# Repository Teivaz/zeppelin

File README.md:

# Zeppelin 

### Airship project with all electrical circuits, PCBs, blueprints, software sources and calculations

### Intended result
First version of this zeppelin should be able to keep itself up in the sky for a decent amount of time. It will be controled remotely (probably via iphone). Total length of airship 168.13cm. Volume 0.46 m3.
In the end it should look like this:    

### Progress
 - [X] Calculate the overall size, mass, and lifting force of the aerostat
 - [X] Create patterns for aerostat
 - [X] Create electrical schemas
 - [X] Design software architecture
 - [ ] Create and debug airship's software
 - [ ] Create software for controlling unit
 - [ ] Trace PCBs and make all PCBs
 - [ ] Assemble aerostat
 - [ ] Field tests

### Calculations
Here is the [link](https://docs.google.com/spreadsheets/d/1KFVUaK0Eav1PAXg2VrwWtU-BHmDxbaWGcJfdvVmI2J4/edit?usp=sharing) to spreadsheet with calculation I made for the lifting force and mass of the airship 

### Mechanics
Most parts used here were thoroughly measured and calculated. Like these cases for motors and servos (feather module)   

### Electronic schematics and PCBs
Well there's not much to say about schematics despite the fact that I'm using ST microcontroller stm32l011f4 and transmitting modules nRF24013. It is designed and traced with [EAGLE](https://www.autodesk.com/products/eagle/overview).

### Software
I am using smt32l011 and the IDE is [VS Code](https://code.visualstudio.com). The language is C with HAL library.

### Version 1.0 considerations
 * Feather MCU should use internal PWM channels directly. This will simplify code and increase working frequency.
 * Feather should use a motor driver that does not short circuit when in low phase of the PWM.
 * Consider using 8 bit controller for the Feather module.

### Further plans
 * Second version will be able to carry a camera.
 * Third version will automatically keep position, folow the route or target.

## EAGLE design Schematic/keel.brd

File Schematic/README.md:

# Change log

## Version 1.1
Status: In development
Changes:
 - [Keel] Added power regulator.
 - [Keel] Measuring Bat0 through divider.
 - [Feather] Changed pinout for PWM.

## Version 1.0.1
Status: Upgraded from v1.0.0
Changes:
 - [Keel] Replaced vertical connectors with horizontal (fixed connector pin numbers).
 - [Keel] Fixed LED polarity.
 - [Keel] Changed voltage divider resistor.
 - [Keel] Flipped the power switch.

## Version 1.0.0
Status: Manufactured

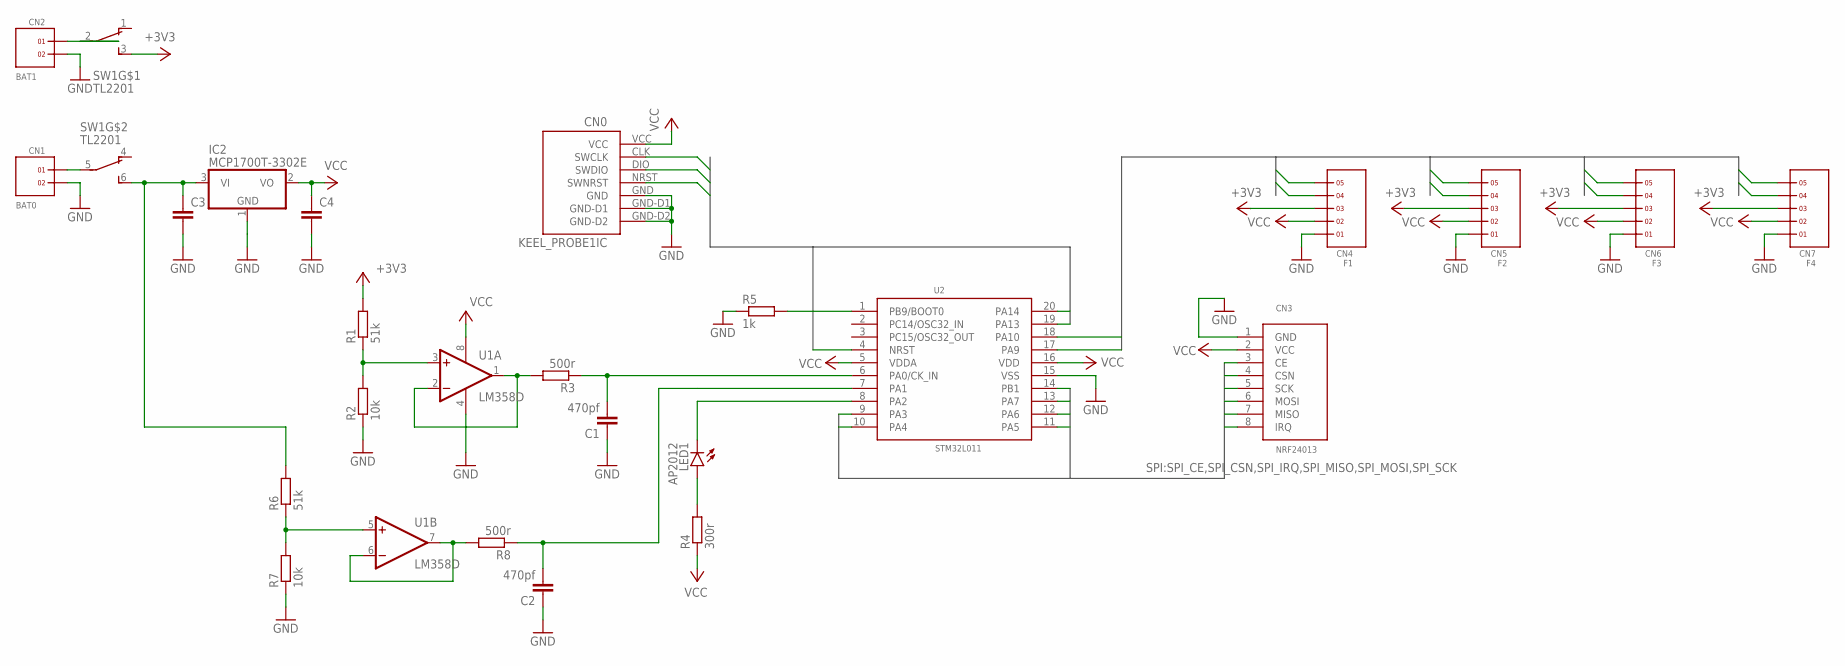
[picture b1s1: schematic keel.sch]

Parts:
C1, C2: 470pf; C0805
C3, C4: C-EUC0805; C0805
CN0: KEEL_PROBE1IC; KEEL_PROBE-IC1
CN1: BAT0; 1X2
CN2: BAT1; 1X2
CN3: NRF24013; PIN
CN4: F1; 1X5H
CN5: F2; 1X5H
CN6: F3; 1X5H
CN7: F4; 1X5H
IC2: MCP1700T-3302E; SOT23
LED1: AP2012
R1, R6: 51k; R0805
R2, R7: 10k; R0805
R3, R8: 500r; R0805
R4: 300r; R0805
R5: 1k; R0805
SW1: TL2201
U1: LM358D; SO08
U2: STM32L011; SSOP20

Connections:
+3V3: CN4.3, CN5.3, CN6.3, CN7.3, R1.2, SW1.3
GND: C1.1, C2.1, C3.2, C4.2, CN0.GND, CN0.GND-D1, CN0.GND-D2, CN1.2, CN2.2, CN3.1 (GND), CN4.1, CN5.1, CN6.1, CN7.1, IC2.1 (GND), R2.1, R5.1, R7.1, U1.4 (V-), U2.15 (VSS)
I2C_SCL: CN4.4, CN5.4, CN6.4, CN7.4, U2.17 (PA9)
I2C_SDA: CN4.5, CN5.5, CN6.5, CN7.5, U2.18 (PA10)
unnamed: R1.1, R2.2, U1.3 (+IN)
unnamed: LED1.C, U2.8 (PA2)
unnamed: LED1.A, R4.2
unnamed: C1.2, R3.1, U2.6 (PA0/CK_IN)
unnamed: R5.2, U2.1 (PB9/BOOT0)
unnamed: R3.2, U1.1 (OUT), U1.2 (-IN)
unnamed: CN2.1, SW1.2
unnamed: CN1.1, SW1.5 (2)
unnamed: R8.2, U1.6 (-IN), U1.7 (OUT)
unnamed: R6.1, R7.2, U1.5 (+IN)
unnamed: C2.2, R8.1, U2.7 (PA1)
unnamed: C3.1, IC2.3 (VI), R6.2, SW1.6 (3)
NRST: CN0.NRST (SWNRST), U2.4 (NRST)
SPI_CE: CN3.3 (CE), U2.10 (PA4)
SPI_CSN: CN3.4 (CSN), U2.9 (PA3)
SPI_IRQ: CN3.8 (IRQ), U2.14 (PB1)
SPI_MISO: CN3.7 (MISO), U2.12 (PA6)
SPI_MOSI: CN3.6 (MOSI), U2.13 (PA7)
SPI_SCK: CN3.5 (SCK), U2.11 (PA5)
SWCLK: CN0.CLK (SWCLK), U2.20 (PA14)
SWDIO: CN0.DIO (SWDIO), U2.19 (PA13)
VCC: C4.1, CN0.VCC, CN3.2 (VCC), CN4.2, CN5.2, CN6.2, CN7.2, IC2.2 (VO), R4.1, U1.8 (V+), U2.5 (VDDA), U2.16 (VDD)

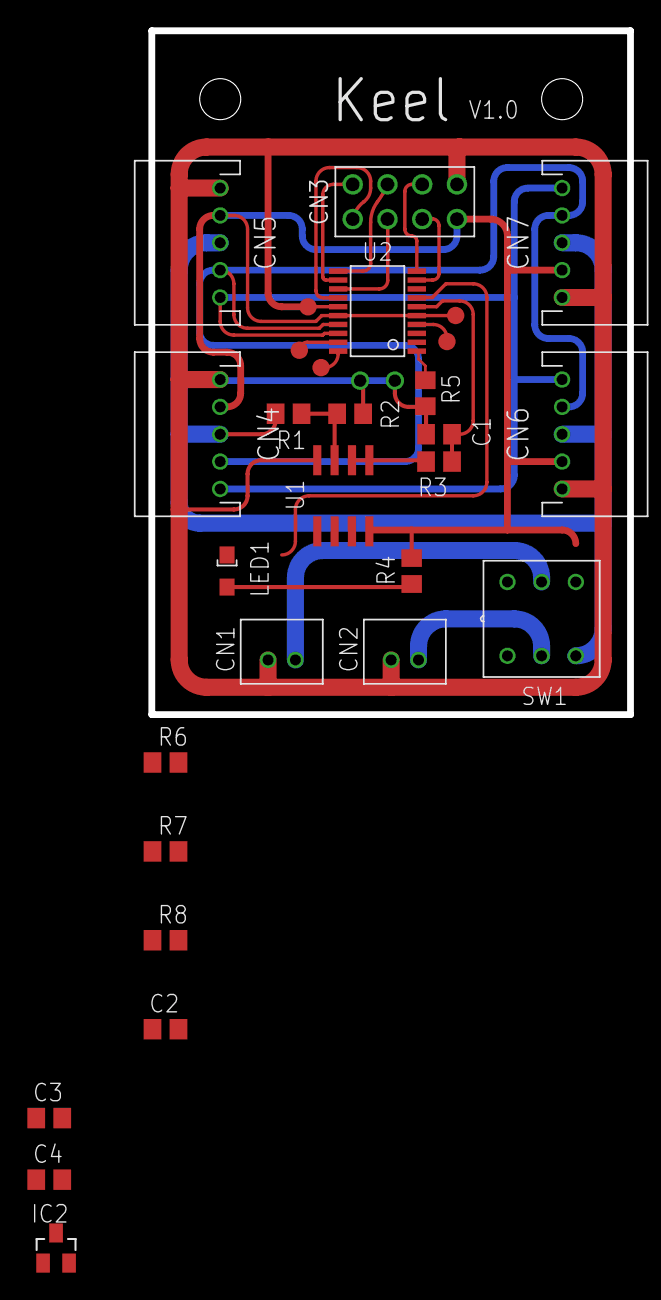
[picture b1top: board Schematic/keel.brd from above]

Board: 2 copper layers, 35.0 x 50.0 mm, 26 parts (1 on the bottom side), 26 nets.

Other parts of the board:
E$5: ZEPPELIN

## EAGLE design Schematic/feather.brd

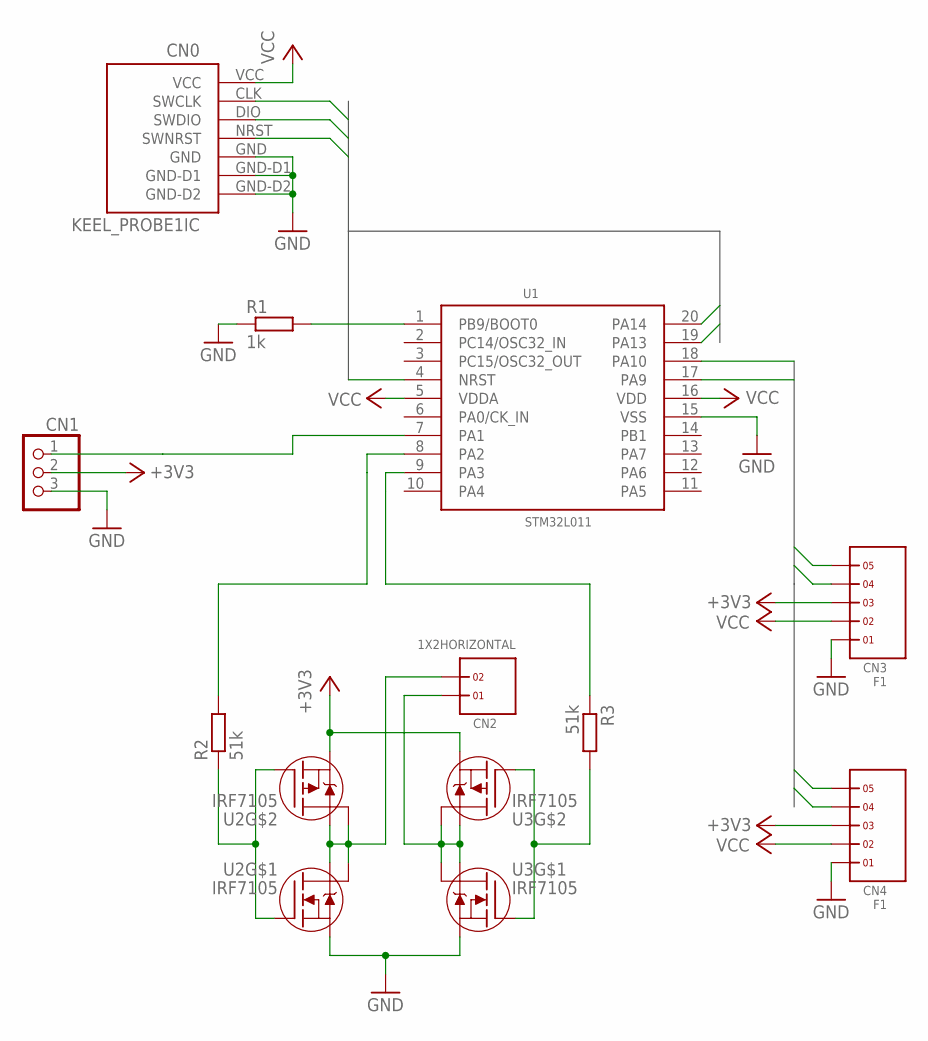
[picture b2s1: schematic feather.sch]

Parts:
CN0: KEEL_PROBE1IC; KEEL_PROBE-IC1
CN1: PINHD-1X3/90; 1X03/90
CN2: 1X2HORIZONTAL; 1X2H
CN3, CN4: F1; 1X5H
R1: 1k; R0805
R2, R3: 51k; R0805
U1: STM32L011; SSOP20
U2, U3: IRF7105; SO8-2

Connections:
+3V3: CN1.2, CN3.3, CN4.3, U2.3 (S), U3.3 (S)
GND: CN0.GND, CN0.GND-D1, CN0.GND-D2, CN1.3, CN3.1, CN4.1, R1.1, U1.15 (VSS), U2.1 (S), U3.1 (S)
I2C_SCL: CN3.4, CN4.4, U1.17 (PA9)
I2C_SDA: CN3.5, CN4.5, U1.18 (PA10)
unnamed: CN2.2, U2.5 (D), U2.6 (D), U2.7 (D), U2.8 (D)
unnamed: R3.1, U1.9 (PA3)
unnamed: R3.2, U3.2 (G), U3.4 (G)
unnamed: CN2.1, U3.5 (D), U3.6 (D), U3.7 (D), U3.8 (D)
unnamed: R2.2, U1.8 (PA2)
unnamed: R2.1, U2.2 (G), U2.4 (G)
unnamed: R1.2, U1.1 (PB9/BOOT0)
unnamed: CN1.1, U1.7 (PA1)
NRST: CN0.NRST (SWNRST), U1.4 (NRST)
SWCLK: CN0.CLK (SWCLK), U1.20 (PA14)
SWDIO: CN0.DIO (SWDIO), U1.19 (PA13)
VCC: CN0.VCC, CN3.2, CN4.2, U1.5 (VDDA), U1.16 (VDD)

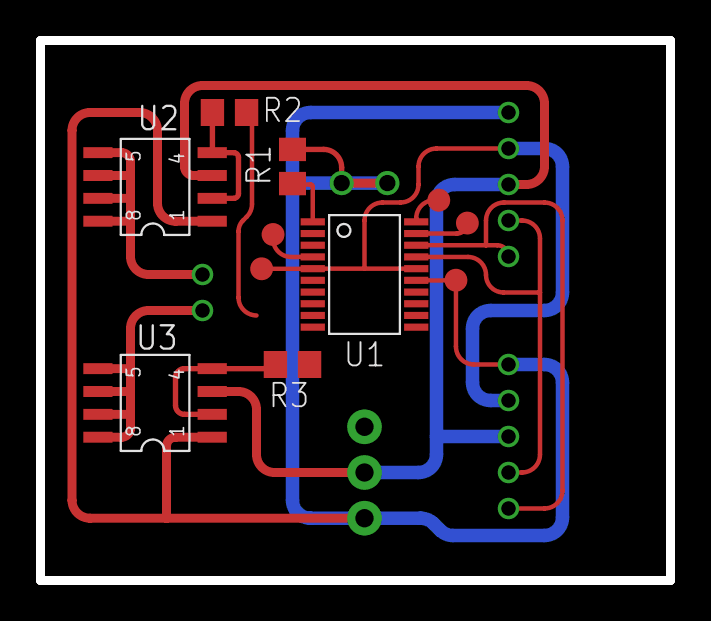
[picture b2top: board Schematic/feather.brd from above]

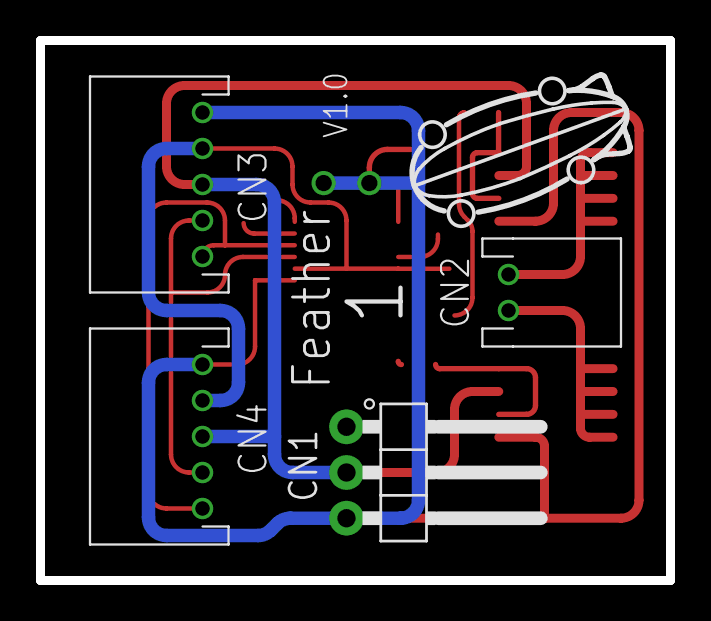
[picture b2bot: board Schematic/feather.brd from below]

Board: 2 copper layers, 35.0 x 30.0 mm, 12 parts (5 on the bottom side), 16 nets.

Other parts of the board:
E$5: ZEPPELIN

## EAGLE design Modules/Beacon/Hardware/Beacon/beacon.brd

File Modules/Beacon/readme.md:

# The Beacon module

This module is used only for testing purposes.

Every second the beacon tramsmits data that should be picked up by the device.

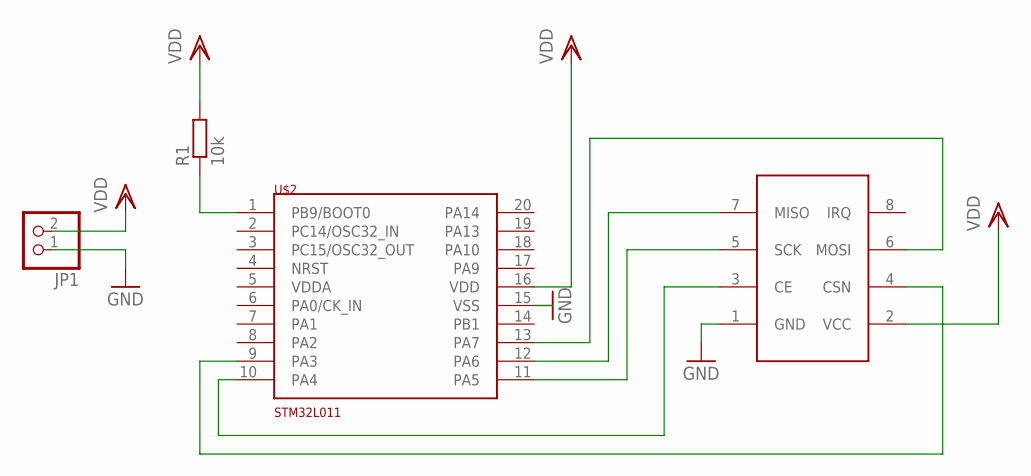
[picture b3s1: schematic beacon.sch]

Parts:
JP1: PINHD-1X2; 1X02
R1: 10k; R0805
U$1: RF24013; PIN
U$2: STM32L011; SSOP20

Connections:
CE: U$1.3 (CE), U$2.10 (PA4)
CSN: U$1.4 (CSN), U$2.9 (PA3)
GND: JP1.1, U$1.1 (GND), U$2.15 (VSS)
MISO: U$1.7 (MISO), U$2.12 (PA6)
MOSI: U$1.6 (MOSI), U$2.13 (PA7)
unnamed: R1.1, U$2.1 (PB9/BOOT0)
SCK: U$1.5 (SCK), U$2.11 (PA5)
VDD: JP1.2, R1.2, U$1.2 (VCC), U$2.16 (VDD)
VDDA: U$2.5 (VDDA)

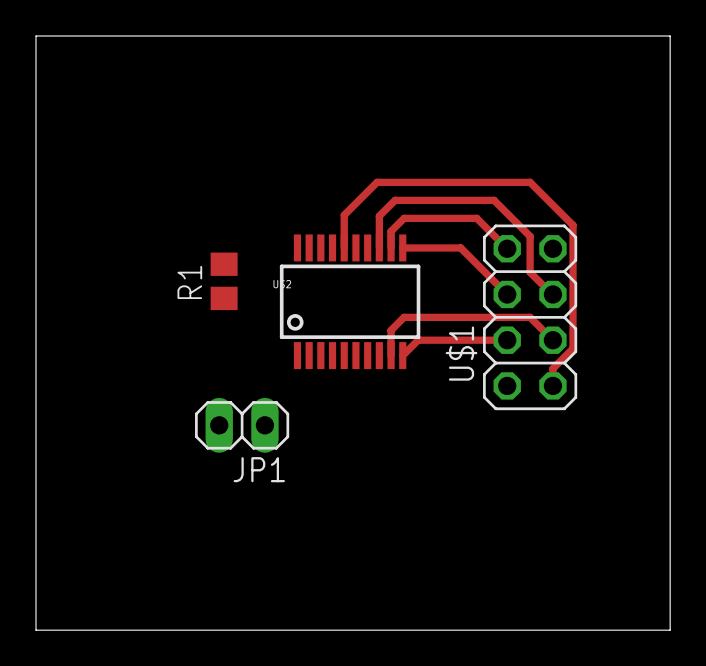
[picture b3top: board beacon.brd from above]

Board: 2 copper layers, 35.2 x 33.0 mm, 4 parts (0 on the bottom side), 8 nets.

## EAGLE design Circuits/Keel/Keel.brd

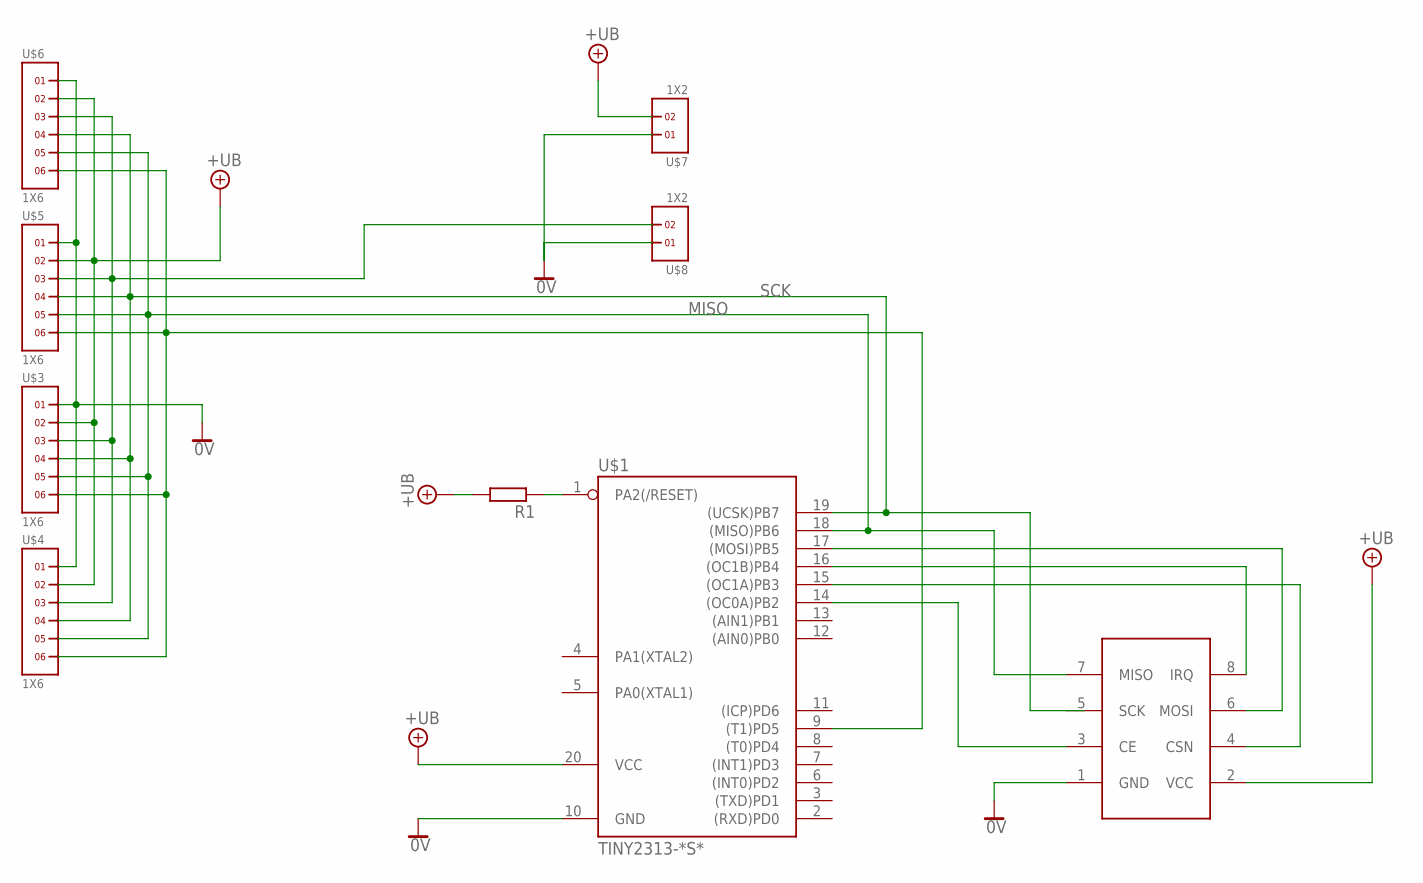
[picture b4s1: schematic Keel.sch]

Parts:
R1: R-EU_M1206; M1206
U$1: TINY2313-*S*; SO20L$
U$2: RF24013; PIN
U$3, U$4, U$5, U$6: 1X6
U$7, U$8: 1X2

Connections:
0V: U$1.10 (GND), U$2.1 (GND), U$3.1, U$4.1, U$5.1, U$6.1, U$7.1, U$8.1
+UB: R1.2, U$1.20 (VCC), U$2.2 (VCC), U$3.2, U$4.2, U$5.2, U$6.2, U$7.2
MISO: U$1.18 ((MISO)PB6), U$2.7 (MISO), U$3.5, U$4.5, U$5.5, U$6.5
unnamed: R1.1, U$1.1 (PA2(/RESET))
unnamed: U$1.17 ((MOSI)PB5), U$2.6 (MOSI)
unnamed: U$1.16 ((OC1B)PB4), U$2.8 (IRQ)
unnamed: U$1.14 ((OC0A)PB2), U$2.3 (CE)
unnamed: U$3.3, U$4.3, U$5.3, U$6.3, U$8.2
unnamed: U$1.15 ((OC1A)PB3), U$2.4 (CSN)
unnamed: U$1.9 ((T1)PD5), U$3.6, U$4.6, U$5.6, U$6.6
SCK: U$1.19 ((UCSK)PB7), U$2.5 (SCK), U$3.4, U$4.4, U$5.4, U$6.4

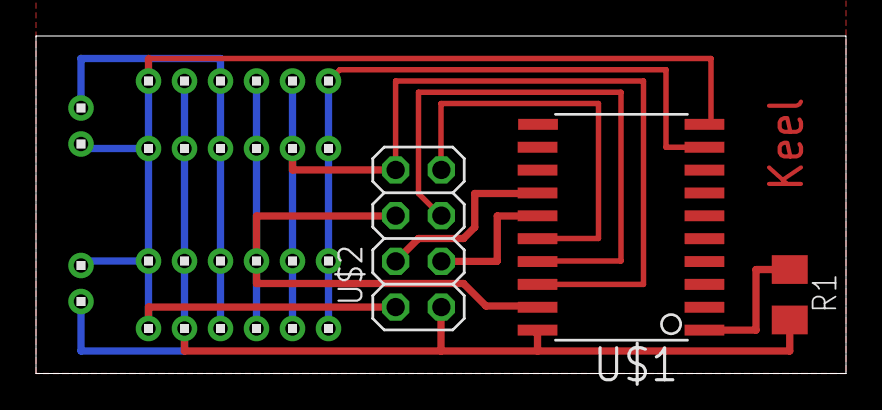
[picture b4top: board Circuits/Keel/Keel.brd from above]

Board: 2 copper layers, 45.0 x 18.8 mm, 9 parts (0 on the bottom side), 11 nets.

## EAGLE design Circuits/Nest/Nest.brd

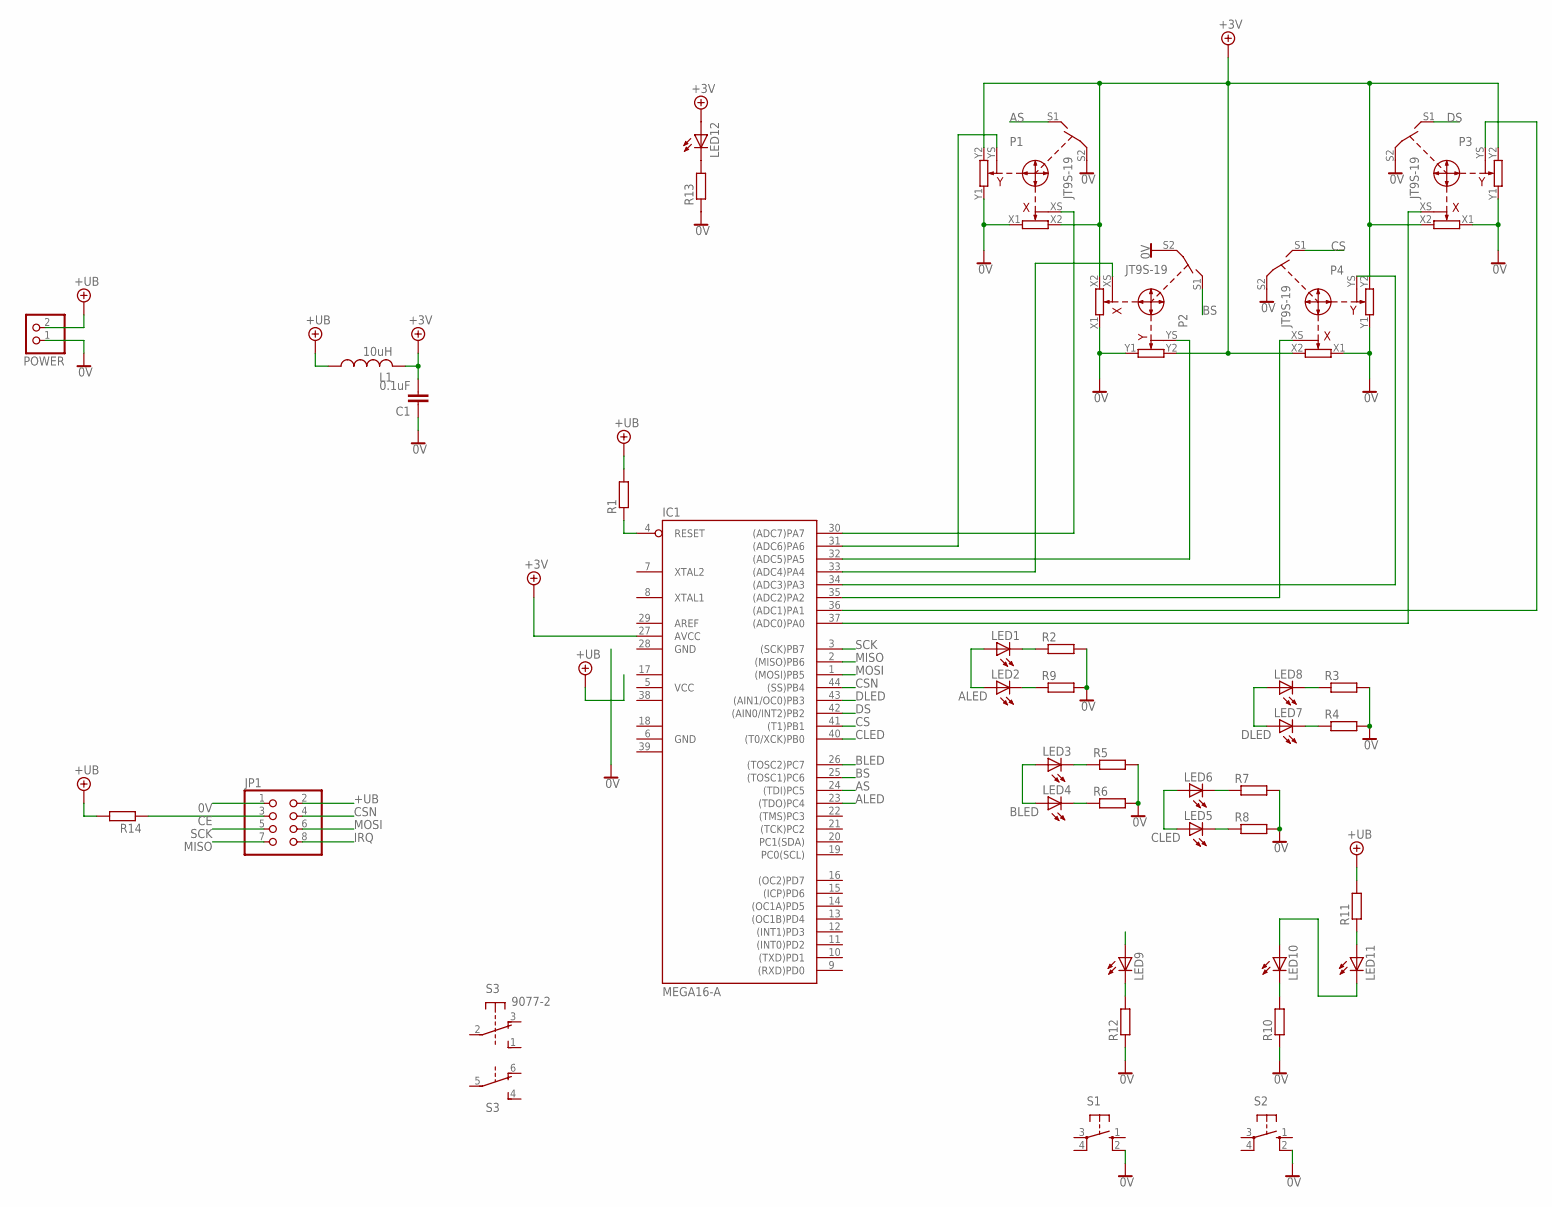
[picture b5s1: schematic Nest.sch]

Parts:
C1: 0.1uF; C050-024X044
IC1: MEGA16-A; TQFP44
JP1: PINHD-2X4; 2X04
L1: 10uH; 0204/7
LED1, LED2, LED3, LED4, LED5, LED6, LED7, LED8, LED9, LED10, LED11, LED12: LED3MM
P1, P2, P3, P4: JT9S-19; JT9S-1P
POWER: PINHD-1X2; 1X02
R1, R14: R-EU_R1206; R1206
R2, R3, R4, R5, R6, R7, R8, R9, R10, R11, R12, R13: R-EU_M0805; M0805
S1, S2: 10-XX; B3F-10XX
S3: 9077-2

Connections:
0V: C1.1, JP1.1, P1.S2, P1.X1, P1.Y1, P2.S2, P2.X1, P2.Y1, P3.S2, P3.X1, P3.Y1, P4.S2, P4.X1, P4.Y1, POWER.1, R2.2, R3.2, R4.2, R5.2, R6.2, R7.2, R8.2, R9.2, R10.1, R12.1, R13.1, S1.2 (S1), S2.2 (S1)
+4.1V: C1.2, IC1.27 (AVCC), L1.2, LED12.A, P1.X2, P1.Y2, P2.X2, P2.Y2, P3.X2, P3.Y2, P4.X2, P4.Y2
+UB: JP1.2, L1.1, POWER.2, R1.2, R11.2, R14.2
ALED: IC1.23 ((TDO)PC4), LED1.A, LED2.A
AS: IC1.24 ((TDI)PC5), P1.S1
BLED: IC1.26 ((TOSC2)PC7), LED3.A, LED4.A
BS: IC1.25 ((TOSC1)PC6), P2.S1
CE: JP1.3, R14.1
CLED: IC1.40 ((T0/XCK)PB0), LED5.A, LED6.A
CS: IC1.41 ((T1)PB1), P4.S1
CSN: IC1.44 ((SS)PB4), JP1.4
DLED: IC1.43 ((AIN1/OC0)PB3), LED7.A, LED8.A
DS: IC1.42 ((AIN0/INT2)PB2), P3.S1
GND: IC1.6 (GND), IC1.28 (GND)
GND1: IC1.18 (GND1)
GND2: IC1.39 (GND2)
IRQ: JP1.8
MISO: IC1.2 ((MISO)PB6), JP1.7
MOSI: IC1.1 ((MOSI)PB5), JP1.6
unnamed: LED1.K (C), R2.1
unnamed: LED7.K (C), R4.1
unnamed: IC1.4 (RESET), R1.1
unnamed: IC1.37 ((ADC0)PA0), P3.XS
unnamed: IC1.31 ((ADC6)PA6), P1.YS
unnamed: IC1.32 ((ADC5)PA5), P2.YS
unnamed: IC1.33 ((ADC4)PA4), P2.XS
unnamed: IC1.34 ((ADC3)PA3), P4.YS
unnamed: IC1.35 ((ADC2)PA2), P4.XS
unnamed: LED8.K (C), R3.1
unnamed: IC1.36 ((ADC1)PA1), P3.YS
unnamed: LED4.K (C), R6.1
unnamed: LED3.K (C), R5.1
unnamed: LED6.K (C), R7.1
unnamed: LED5.K (C), R8.1
unnamed: LED2.K (C), R9.1
unnamed: LED10.A, LED11.K (C)
unnamed: LED11.A, R11.1
unnamed: LED10.K (C), R10.2
unnamed: LED9.K (C), R12.2
unnamed: LED12.K (C), R13.2
unnamed: IC1.30 ((ADC7)PA7), P1.XS
SCK: IC1.3 ((SCK)PB7), JP1.5
VCC: IC1.5 (VCC)
VCC1: IC1.17 (VCC1)
VCC2: IC1.38 (VCC2)

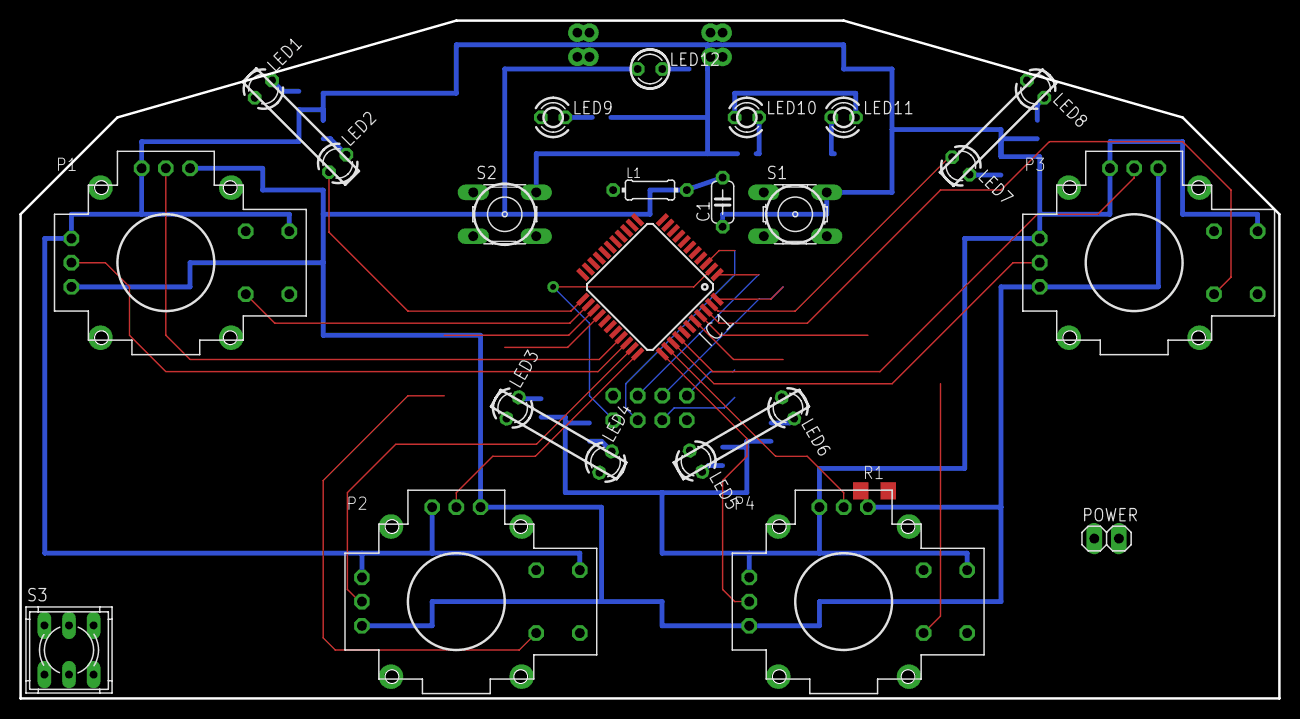
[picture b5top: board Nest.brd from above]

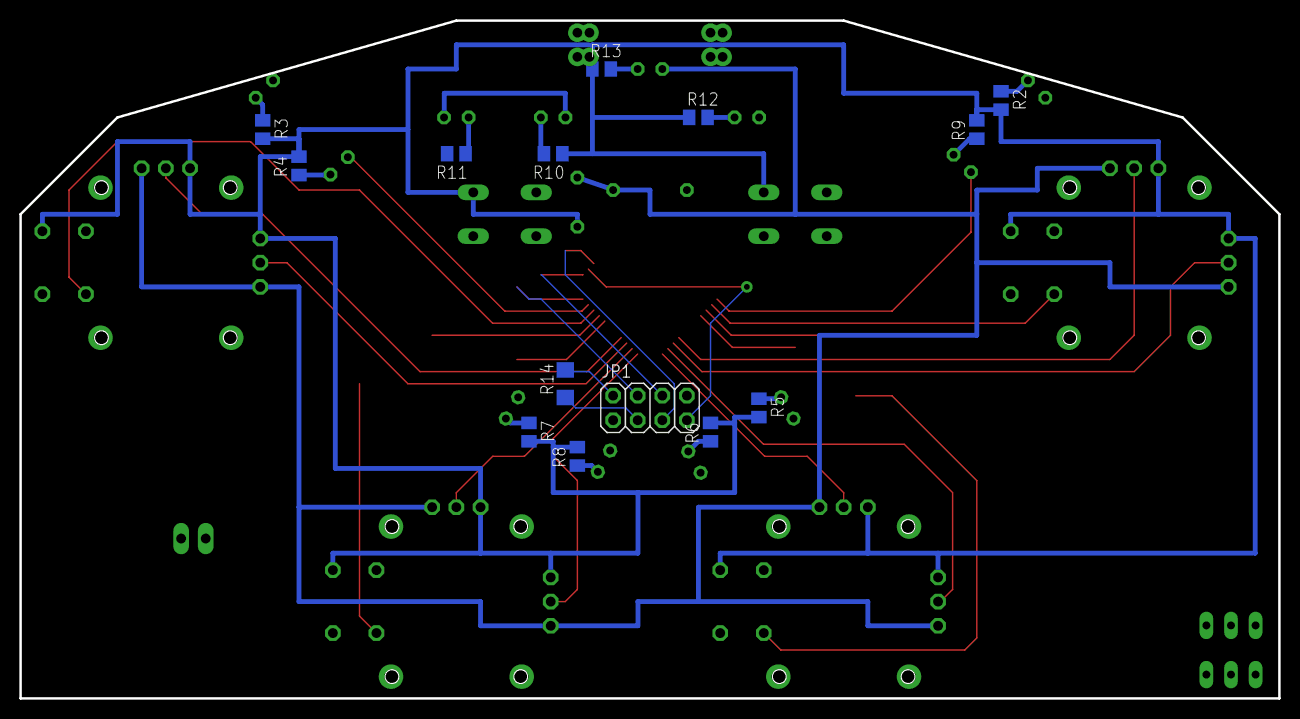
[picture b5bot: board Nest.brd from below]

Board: 2 copper layers, 130.0 x 70.0 mm, 38 parts (14 on the bottom side), 39 nets.

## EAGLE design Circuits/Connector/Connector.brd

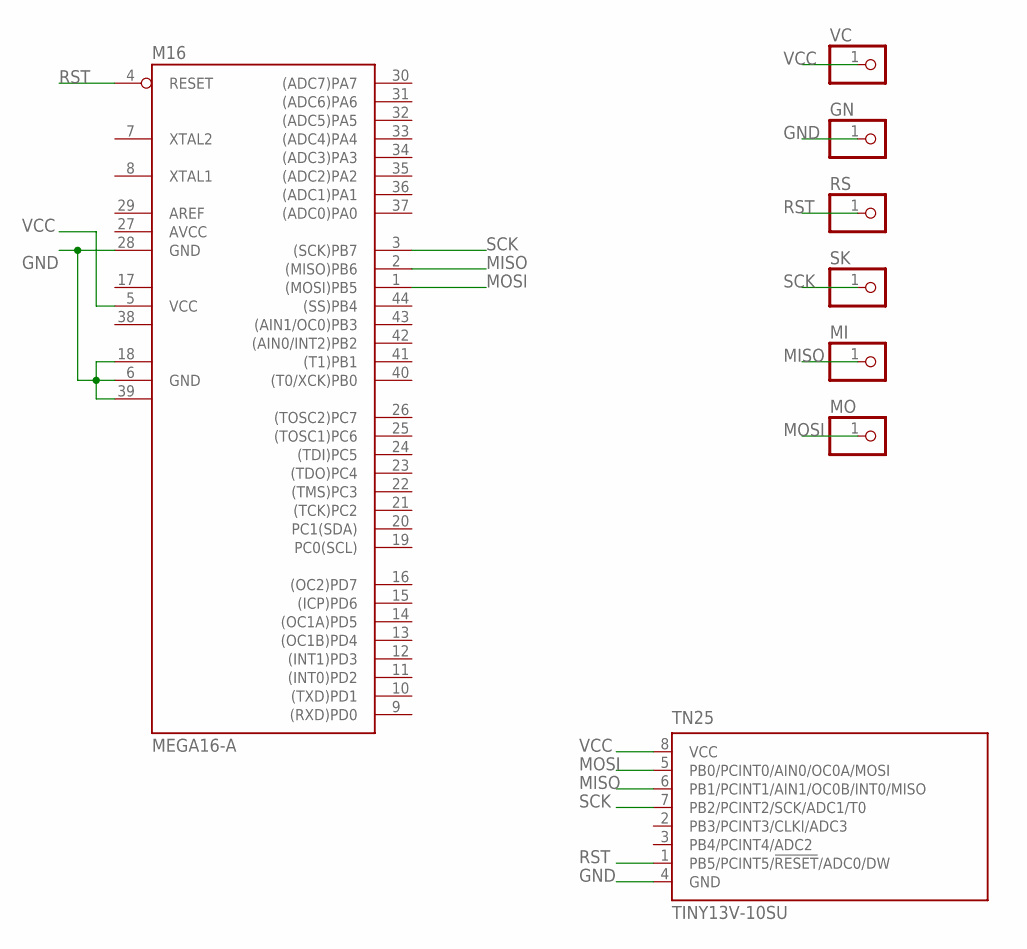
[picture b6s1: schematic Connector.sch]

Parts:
GN: PINHD-1X1; 1X01
M16: MEGA16-A; TQFP44
MI: PINHD-1X1; 1X01
MO: PINHD-1X1; 1X01
RS: PINHD-1X1; 1X01
SK: PINHD-1X1; 1X01
TN25: TINY13V-10SU; 8S2
VC: PINHD-1X1; 1X01

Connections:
AVCC: M16.27 (AVCC)
GND: GN.1, M16.6 (GND), M16.18 (GND1), M16.28 (GND), M16.39 (GND2), TN25.4 (GND)
MISO: M16.2 ((MISO)PB6), MI.1, TN25.6 (PB1/PCINT1/AIN1/OC0B/INT0/MISO)
MOSI: M16.1 ((MOSI)PB5), MO.1, TN25.5 (PB0/PCINT0/AIN0/OC0A/MOSI)
RST: M16.4 (RESET), RS.1, TN25.1 (PB5/PCINT5/!RESET!/ADC0/DW)
SCK: M16.3 ((SCK)PB7), SK.1, TN25.7 (PB2/PCINT2/SCK/ADC1/T0)
VCC: M16.5 (VCC), TN25.8 (VCC), VC.1
VCC1: M16.17 (VCC1)
VCC2: M16.38 (VCC2)

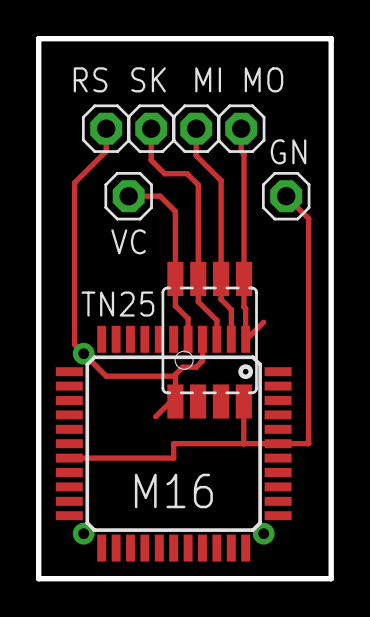
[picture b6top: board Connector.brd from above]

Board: 2 copper layers, 16.2 x 30.0 mm, 8 parts (0 on the bottom side), 6 nets.

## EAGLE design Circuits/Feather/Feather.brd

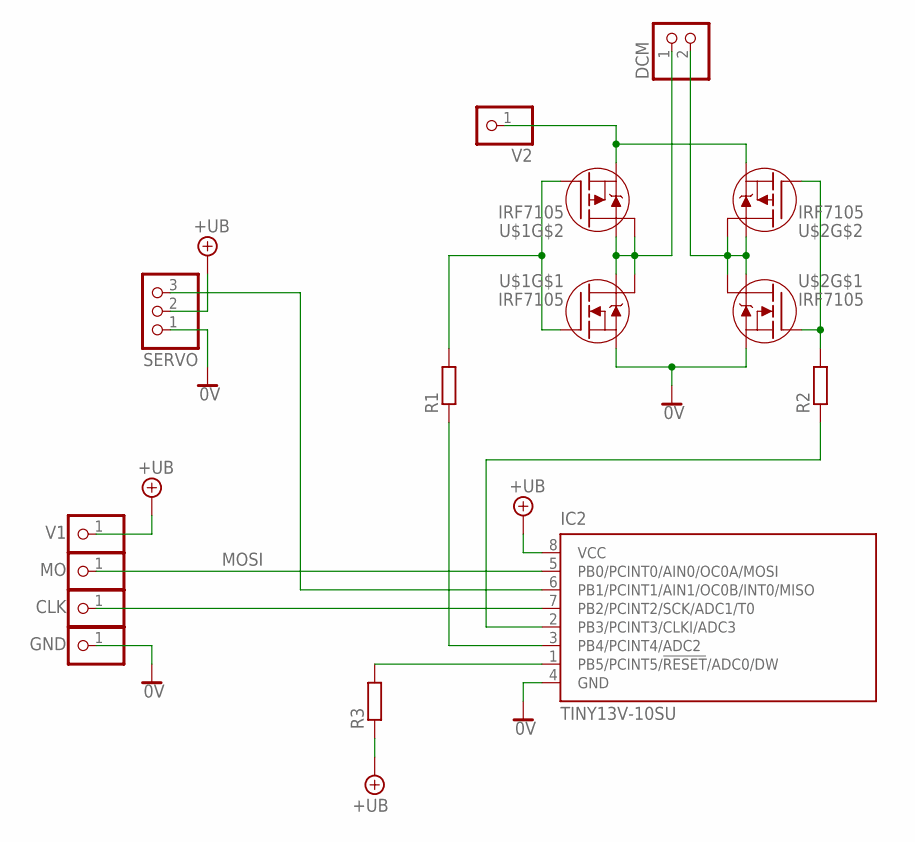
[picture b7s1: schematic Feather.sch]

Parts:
CLK: PINHD-1X1; 1X01
DCM: PINHD-1X2; 1X02
GND: PINHD-1X1; 1X01
IC2: TINY13V-10SU; 8S2
MO: PINHD-1X1; 1X01
R1, R2, R3: R-EU_R1206; R1206
SERVO: PINHD-1X3; 1X03
U$1, U$2: IRF7105; SO8-2
V1, V2: PINHD-1X1; 1X01

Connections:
0V: GND.1, IC2.4 (GND), SERVO.1, U$1.1 (S), U$2.1 (S)
+UB: IC2.8 (VCC), R3.1, SERVO.2, V1.1
MOSI: IC2.5 (PB0/PCINT0/AIN0/OC0A/MOSI), MO.1
unnamed: DCM.1, U$1.5 (D), U$1.6 (D), U$1.7 (D), U$1.8 (D)
unnamed: IC2.3 (PB4/PCINT4/ADC2), R1.1
unnamed: R2.2, U$2.2 (G), U$2.4 (G)
unnamed: DCM.2, U$2.5 (D), U$2.6 (D), U$2.7 (D), U$2.8 (D)
unnamed: IC2.2 (PB3/PCINT3/CLKI/ADC3), R2.1
unnamed: R1.2, U$1.2 (G), U$1.4 (G)
unnamed: IC2.1 (PB5/PCINT5/!RESET!/ADC0/DW), R3.2
unnamed: CLK.1, IC2.7 (PB2/PCINT2/SCK/ADC1/T0)
unnamed: U$1.3 (S), U$2.3 (S), V2.1
unnamed: IC2.6 (PB1/PCINT1/AIN1/OC0B/INT0/MISO), SERVO.3

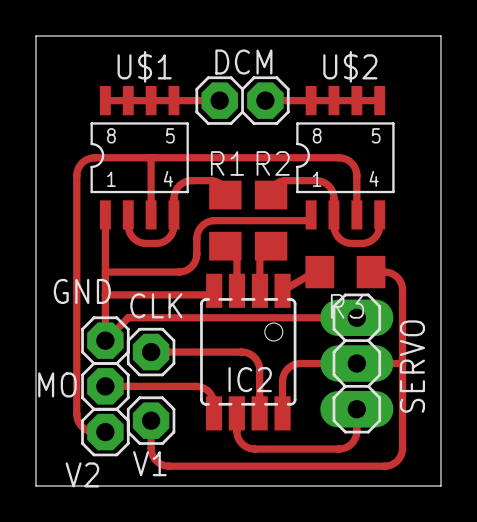
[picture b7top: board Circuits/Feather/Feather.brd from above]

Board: 2 copper layers, 22.5 x 25.0 mm, 13 parts (0 on the bottom side), 13 nets.

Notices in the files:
parts and their libraries:
irf-2: Copyright & License
This library is licensed under the General Public License, Version 2.
More Information about the General Public License is available at http://www.gnu.org/copyleft/gpl.html.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
